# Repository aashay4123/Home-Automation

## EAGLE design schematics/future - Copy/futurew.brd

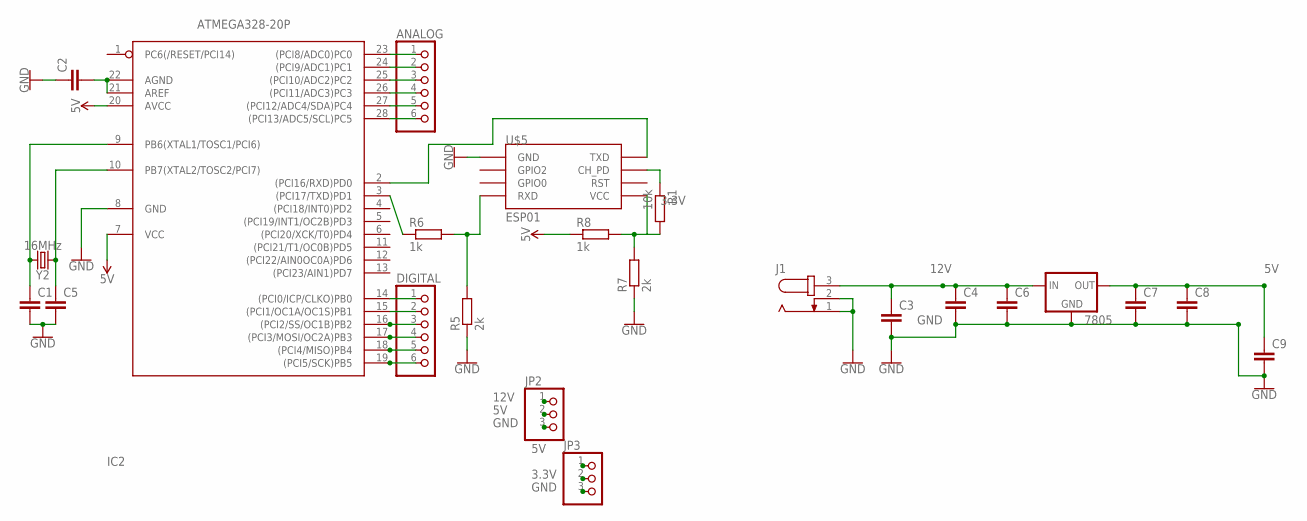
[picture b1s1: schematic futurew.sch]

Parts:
7805: 78XXL
ANALOG: PINHD-1X6; 1X06
C1, C2, C3, C4, C5, C6, C7, C8, C9: C2,5-3; C2.5-3
DIGITAL: PINHD-1X6; 1X06
IC2: ATMEGA328-20P; DIL28-3
J1: JACK-PLUG1; SPC4078
JP2, JP3: PINHD-1X3; 1X03
R1: 10k; 0204/5
R5, R7: 2k; 0204/5
R6, R8: 1k; 0204/5
U$5: ESP01
Y2: 16MHz; HC49US

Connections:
3.3V: JP3.2, R7.2, R8.2, U$5.VCC
5V: 7805.OUT, C7.1, C8.1, C9.1, IC2.7 (VCC), IC2.20 (AVCC), JP2.2, JP3.1, R8.1
12V: 7805.IN, C3.1, C4.1, C6.1, J1.3, JP2.1
GND: 7805.GND, C1.2, C2.1, C3.2, C4.2, C5.2, C6.2, C7.2, C8.2, C9.2, IC2.8 (GND), J1.1, J1.2, JP2.3, JP3.3, R5.1, R7.1, U$5.GND
unnamed: R5.2, R6.2, U$5.RX (RXD)
unnamed: IC2.3 ((PCI17/TXD)PD1), R6.1
unnamed: IC2.2 ((PCI16/RXD)PD0), U$5.TX (TXD)
unnamed: DIGITAL.6, IC2.19 ((PCI5/SCK)PB5)
unnamed: DIGITAL.5, IC2.18 ((PCI4/MISO)PB4)
unnamed: DIGITAL.4, IC2.17 ((PCI3/MOSI/OC2A)PB3)
unnamed: DIGITAL.3, IC2.16 ((PCI2/SS/OC1B)PB2)
unnamed: ANALOG.1, IC2.23 ((PCI8/ADC0)PC0)
unnamed: ANALOG.2, IC2.24 ((PCI9/ADC1)PC1)
unnamed: ANALOG.3, IC2.25 ((PCI10/ADC2)PC2)
unnamed: C2.2, IC2.21 (AREF), IC2.22 (AGND)
unnamed: ANALOG.4, IC2.26 ((PCI11/ADC3)PC3)
unnamed: ANALOG.5, IC2.27 ((PCI12/ADC4/SDA)PC4)
unnamed: ANALOG.6, IC2.28 ((PCI13/ADC5/SCL)PC5)
unnamed: DIGITAL.1, IC2.14 ((PCI0/ICP/CLKO)PB0)
unnamed: DIGITAL.2, IC2.15 ((PCI1/OC1A/OC1S)PB1)
unnamed: R1.1, U$5.CH_PD
unnamed: C5.1, IC2.10 (PB7(XTAL2/TOSC2/PCI7)), Y2.1
unnamed: C1.1, IC2.9 (PB6(XTAL1/TOSC1/PCI6)), Y2.2

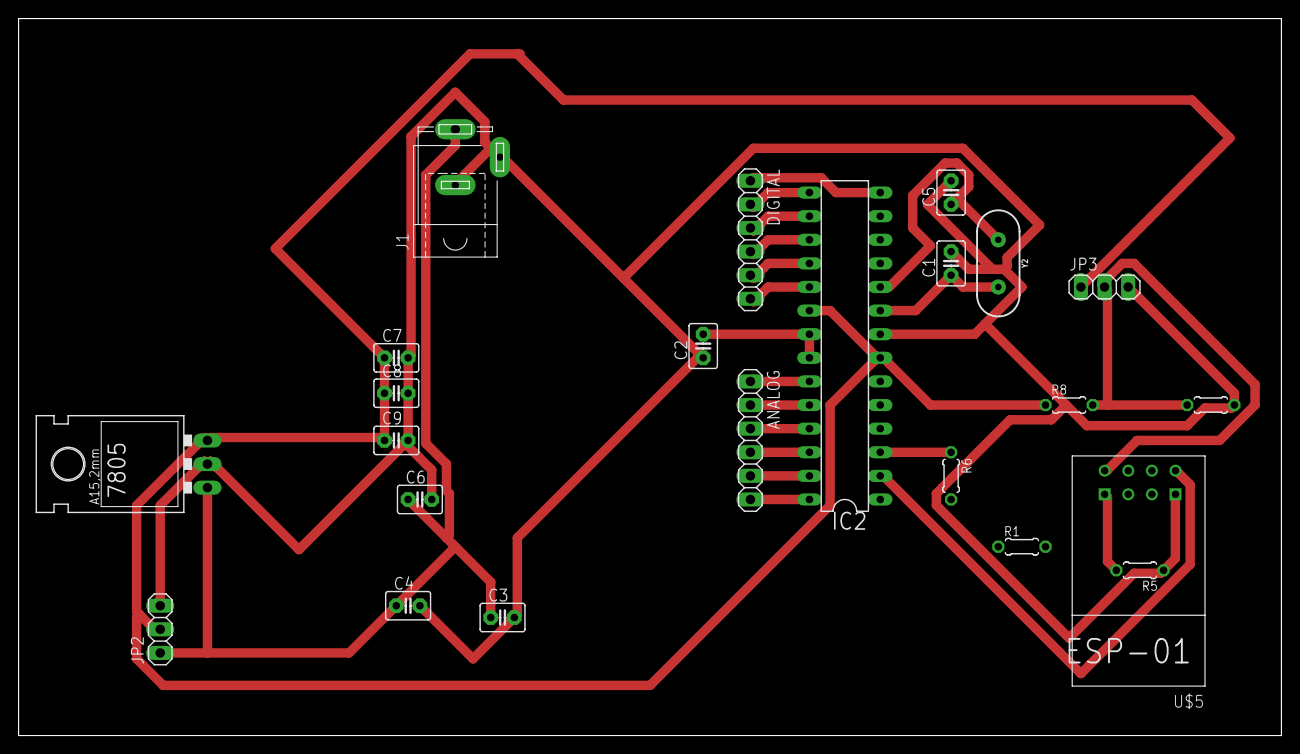
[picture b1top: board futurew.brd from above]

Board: 2 copper layers, 135.9 x 77.1 mm, 23 parts (0 on the bottom side), 23 nets.

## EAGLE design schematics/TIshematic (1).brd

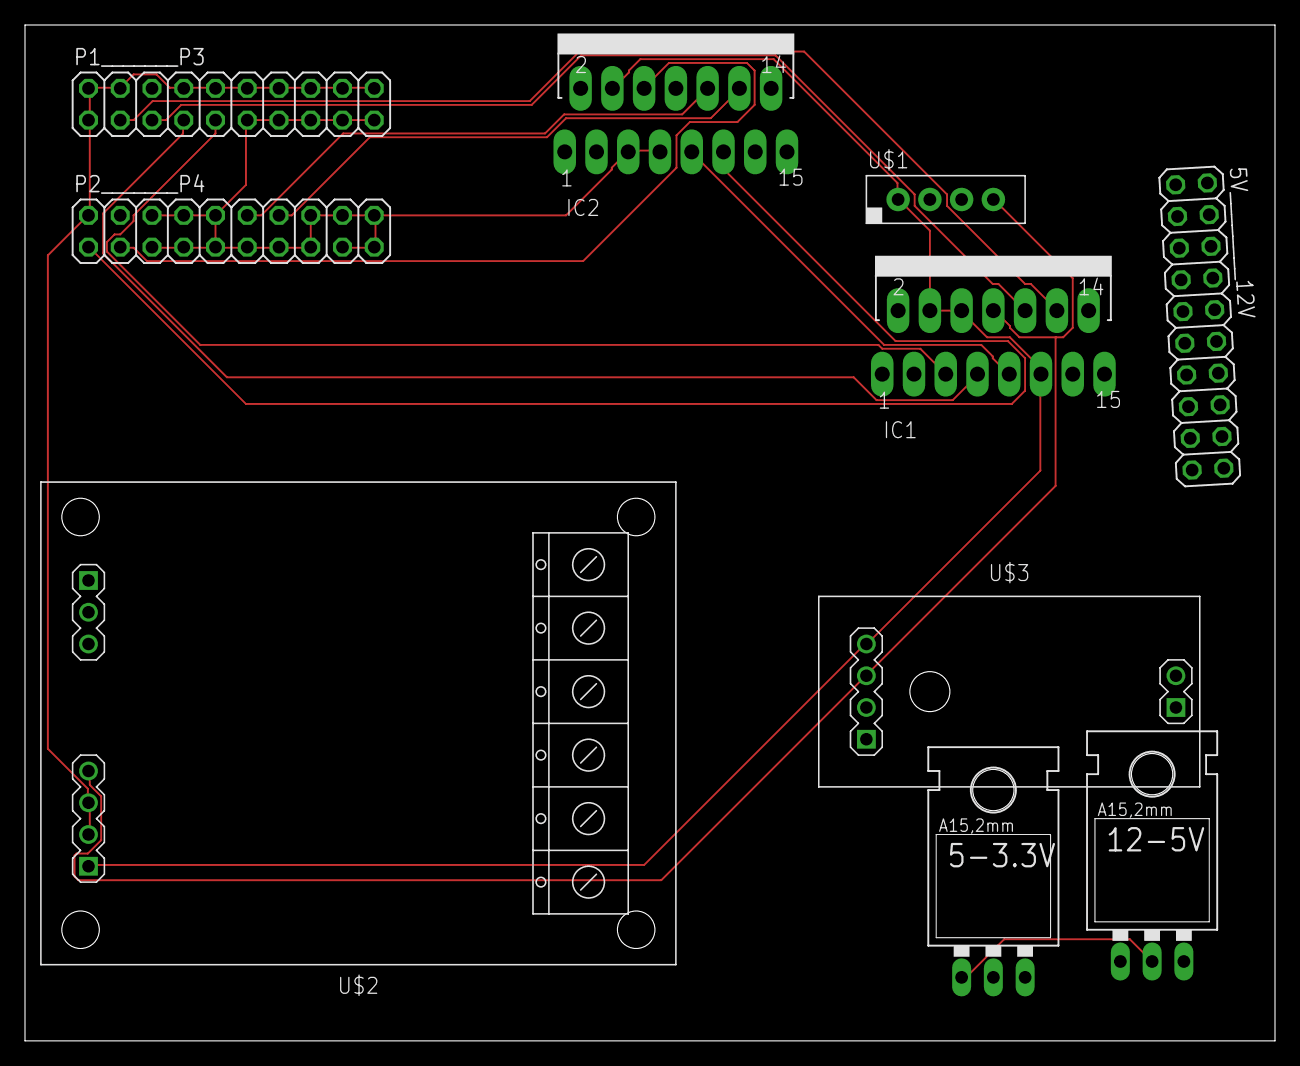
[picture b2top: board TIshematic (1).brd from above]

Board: 2 copper layers, 100.0 x 81.3 mm, 10 parts (0 on the bottom side), 13 nets.

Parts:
5-3.3V, 12-5V: 78XXL
5V________12V: 2X10
IC1, IC2: L298; MULTIWATT-15
P1_______P3, P2_______P4: 2X10
U$1: DHT11
U$2: RELAY-2-SRD
U$3: SOIL-MOISTURE-SENSOR

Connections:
2: IC2.5, IC2.7, P1_______P3.1, P1_______P3.2, P1_______P3.4, P1_______P3.8, P1_______P3.10, P1_______P3.11, P1_______P3.12, P1_______P3.13, P1_______P3.14, P1_______P3.15, P1_______P3.16, P1_______P3.17, P1_______P3.18, P1_______P3.19, P1_______P3.20, P2_______P4.2, P2_______P4.5, P2_______P4.6, P2_______P4.7, P2_______P4.8, P2_______P4.9, P2_______P4.10, P2_______P4.11, P2_______P4.13, P2_______P4.15, P2_______P4.16, P2_______P4.17, P2_______P4.18, P2_______P4.19, P2_______P4.20, U$2.J1.2, U$2.J1.3
40: IC2.11, P2_______P4.1
+5V: IC1.4, IC1.6, IC1.11, IC2.4, U$1.1, U$2.J1.1, U$3.J1.4
+12V: IC1.9, IC2.9
GND: IC1.8, IC2.8, U$1.4, U$2.J1.4, U$3.J1.3
unnamed: IC2.12, P2_______P4.14
unnamed: IC1.12, P1_______P3.3
unnamed: IC1.10, P1_______P3.5
unnamed: IC1.7, P1_______P3.7
unnamed: IC1.5, P1_______P3.9
unnamed: IC2.6, P2_______P4.3
unnamed: 5-3.3V.IN, 12-5V.GND
unnamed: IC2.10, P2_______P4.12

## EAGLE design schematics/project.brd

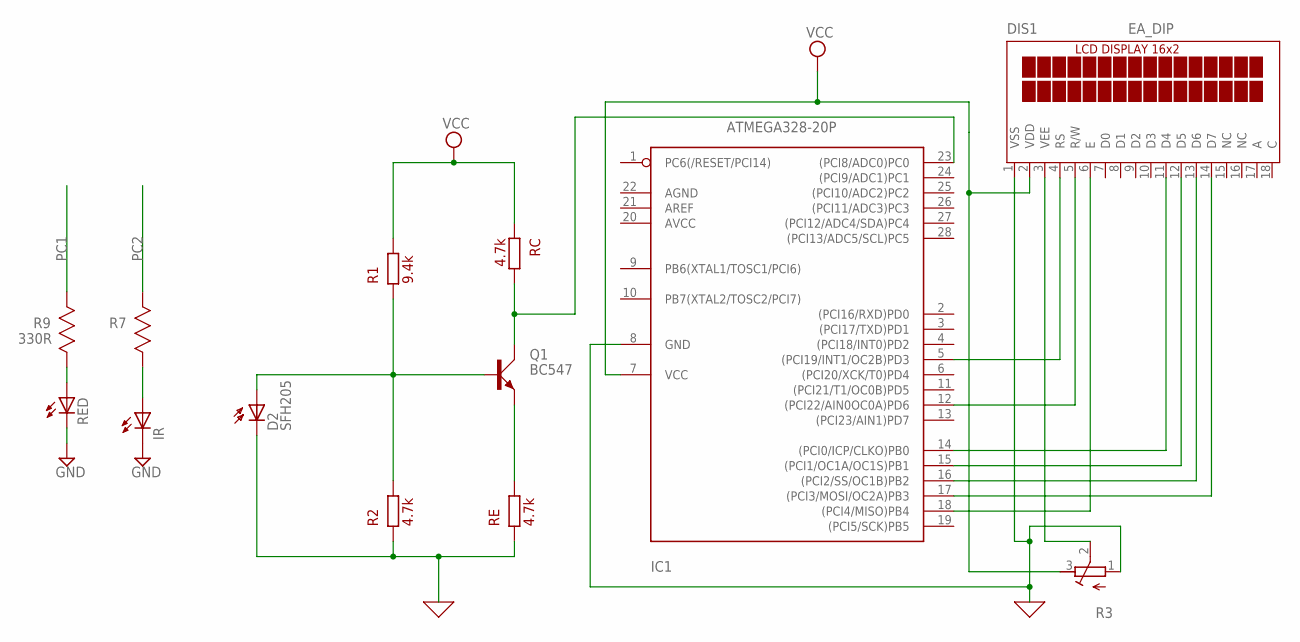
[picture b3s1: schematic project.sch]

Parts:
D2: SFH205
DIS1: EA_DIP
IC1: ATMEGA328-20P; DIL28-3
IR: LEDCHIP-LED0603; CHIP-LED0603
Q1: BC547; SOT54A
R3: R-TRIMM4G/J; RTRIM4G/J
R7, R9: 330R; RESC1608X60N
RED: LEDCHIP-LED0603; CHIP-LED0603

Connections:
0: D2.K (C), DIS1.1 (VSS), IC1.8 (GND), R3.1 (A)
GND: IR.C, RED.C
unnamed: IR.A, R7.2 (R2)
unnamed: IC1.23 ((PCI8/ADC0)PC0), Q1.C
unnamed: R9.2 (R2), RED.A
unnamed: D2.A, Q1.B
unnamed: DIS1.4 (RS), IC1.5 ((PCI19/INT1/OC2B)PD3)
unnamed: DIS1.5 (R/W), IC1.12 ((PCI22/AIN0OC0A)PD6)
unnamed: DIS1.6 (E), IC1.18 ((PCI4/MISO)PB4)
unnamed: DIS1.11 (D4), IC1.14 ((PCI0/ICP/CLKO)PB0)
unnamed: DIS1.12 (D5), IC1.15 ((PCI1/OC1A/OC1S)PB1)
unnamed: DIS1.13 (D6), IC1.16 ((PCI2/SS/OC1B)PB2)
unnamed: DIS1.14 (D7), IC1.17 ((PCI3/MOSI/OC2A)PB3)
unnamed: DIS1.3 (VEE), R3.2 (S)
PC1: R9.1 (R1)
PC2: R7.1 (R1)
VCC: DIS1.2 (VDD), IC1.7 (VCC), R3.3 (E)

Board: 2 copper layers, 9 parts (0 on the bottom side), 15 nets, no tracks yet.

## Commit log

2022-12-09 merged hardware repos
2022-12-09 [ImgBot] Optimize images
    *Total -- 284.54kb -> 205.46kb (27.79%)
    /schematics/Eagle-Libraries-master/images/FootprintExample.png -- 56.34kb -> 16.49kb (70.73%)
    /schematics/Eagle-Libraries-master/images/SymbolExample.png -- 22.37kb -> 8.21kb (63.28%)
    /hardware/AC-to-DC-Converter-Circuit-Diagram.png -- 9.77kb -> 7.09kb (27.46%)
    /hardware/power-supply-block-diagram.jpg -- 23.16kb -> 19.29kb (16.7%)
    /hardware/Recommended-CAPACITOR-Values.jpg -- 64.44kb -> 54.02kb (16.18%)

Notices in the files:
parts and their libraries:
diy-modules: Released under the Creative Commons Attribution 4.0 International License: http://creativecommons.org/licenses/by/4.0
SparkFun-Clocks: Licensing: Creative Commons ShareAlike 4.0 International - https://creativecommons.org/licenses/by-sa/4.0
